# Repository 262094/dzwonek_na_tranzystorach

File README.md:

# dzwonek_na_tranzystorach
jest to aplikacja dzwonka z lat '80 typu słowik ze standardowego montażu przewlekanego THT, dzwonek został zaadaptowany na obecnie panujący trend miniaturyzacji elektroniki w połączeniu głownie montażu SMD z niektórymi elementami THT (tranzystor PNP BD140, brzęczyk bez generatora, kondensatory elektrolityczne 470uF, przycisk, złącze ARK500/2, potencjometr i kondensator ceramiczny 33nF), dzwonek udało się umieścić w wymiarach 66x37,5 (mm). W dzwonku występuje generator częstotliwości dla dzwonka złożony z przerzerzutnika Schmitta połączonego z układem Sziklaiego (wzmocnienie parametru B na wyjściu układu dla brzęczyka) oraz z przerzutnika monostabilnego jako modulatora generowanego tonu z poprzedniego przerzutnika. Układ może pracować w zasilaniu 9V DC jak i 230V AC po uprzednim zaadoptowaniu. Projekt został przygotowany do samodzielnego wytrawienia na laminacie pokrytym warstwą miedzi.

*** WIECEJ MOICH PROJEKTOW JEST DOSTEPNYCH NA MOIM KONCIE ZAPRASZAM DO ZAPOZANANIA SIE Z NIMI APLIKACJA HEALTH_CHECK ORAZ FINANCIFY***

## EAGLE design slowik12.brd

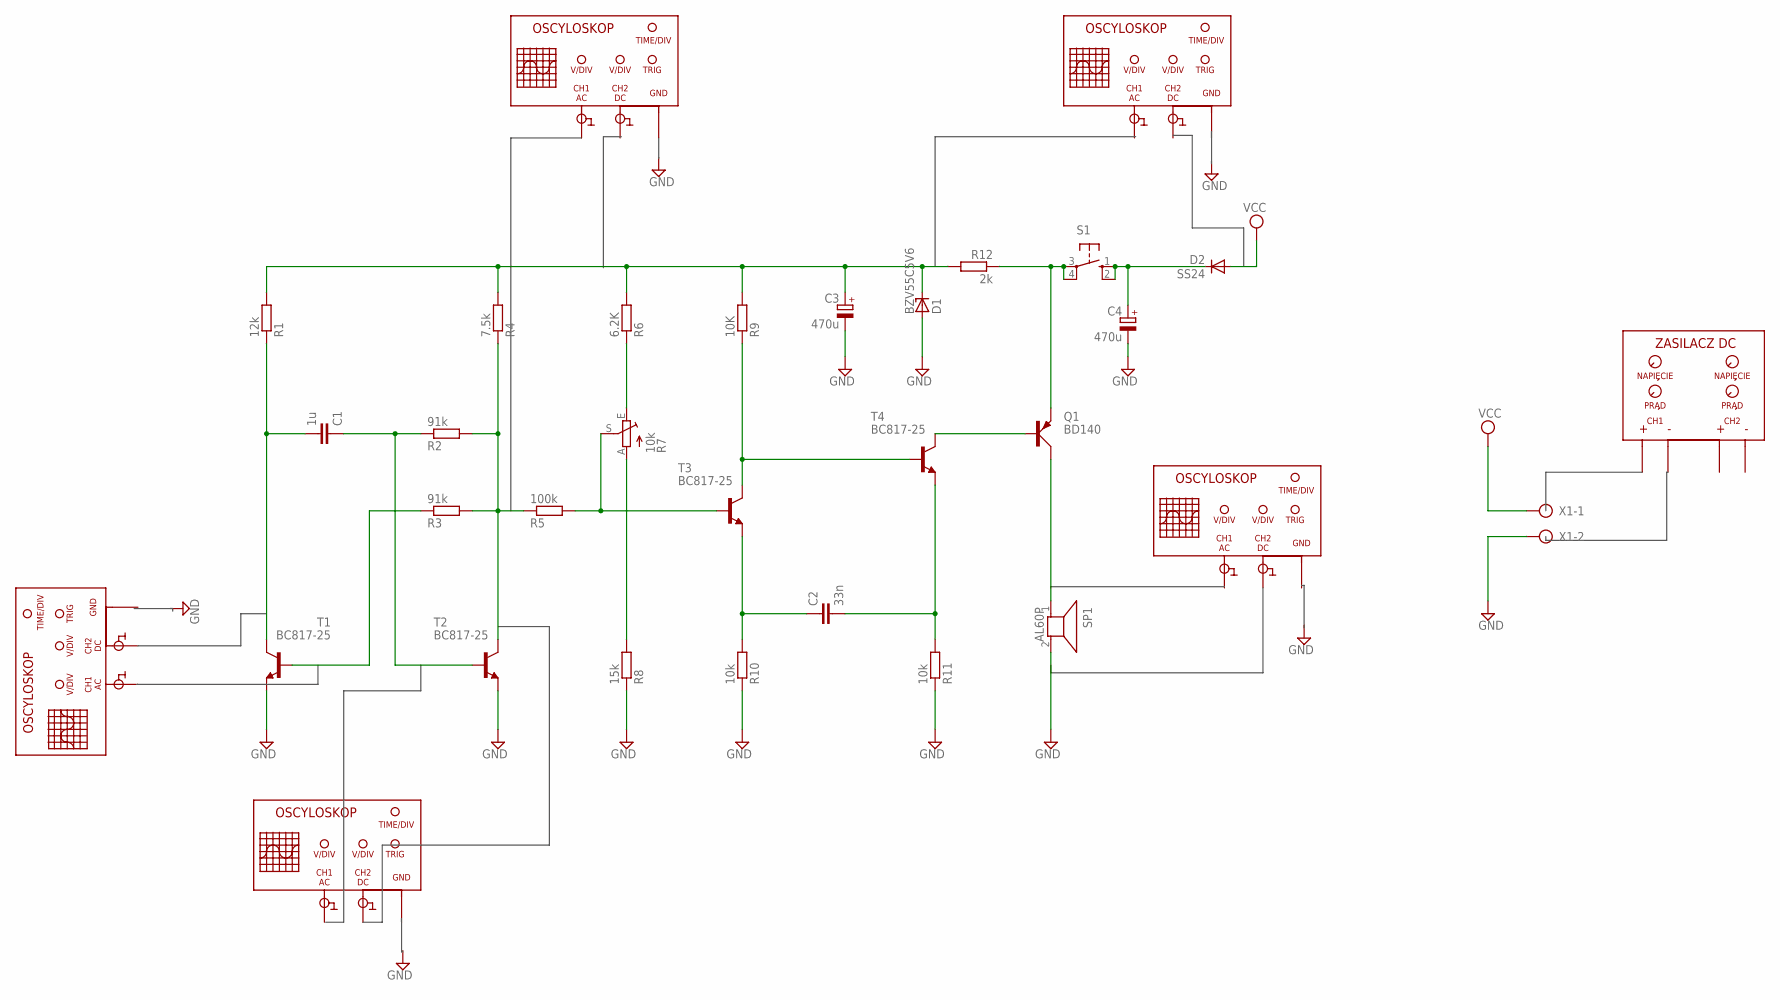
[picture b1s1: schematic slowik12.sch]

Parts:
C1: 1u; C1206
C2: 33n; C2.5-2
C3, C4: 470u; E3,5-8
D1: BZV55C5V6; SOD80C
D2: SS24; SMB
Q1: BD140; TO126AV
R1: 12k; R1206
R2, R3: 91k; R1206
R4: 7.5k; R1206
R5: 100k; R1206
R6: 6.2K; R1206
R7: 10k; PT-10
R8: 15k; R1206
R9: 10K; R1206
R10, R11: 10k; R1206
R12: 2k; R1206
S1: 10-XX; B3F-10XX
SP1: AL60P
T1, T2, T3, T4: BC817-25; SOT23-BEC
U$1, U$2, U$4, U$5, U$6: OSCYLOSKOP_DC_DC; OSCYLOSKOP
U$3: ZASILACZ
X1: AK500/2

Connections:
GND: C3.-, C4.-, D1.A, R8.1, R10.1, R11.1, SP1.2, T1.E, T2.E, X1.2
unnamed: R6.1, R7.E
unnamed: R7.A, R8.2
unnamed: Q1.E, R12.1, S1.3, S1.4 (P1)
unnamed: Q1.C, SP1.1
unnamed: Q1.B, T4.C
unnamed: C2.2, R11.2, T4.E
unnamed: C4.+, D2.C, S1.1 (S), S1.2 (S1)
unnamed: R9.1, T3.C, T4.B
unnamed: C2.1, R10.2, T3.E
unnamed: C1.2, R1.1, T1.C
unnamed: R2.2, R3.2, R4.1, R5.1, T2.C
unnamed: C1.1, R2.1, T2.B
unnamed: R3.1, T1.B
unnamed: R5.2, R7.S, T3.B
unnamed: C3.+, D1.C, R1.2, R4.2, R6.2, R9.2, R12.2
VCC: D2.A, X1.1

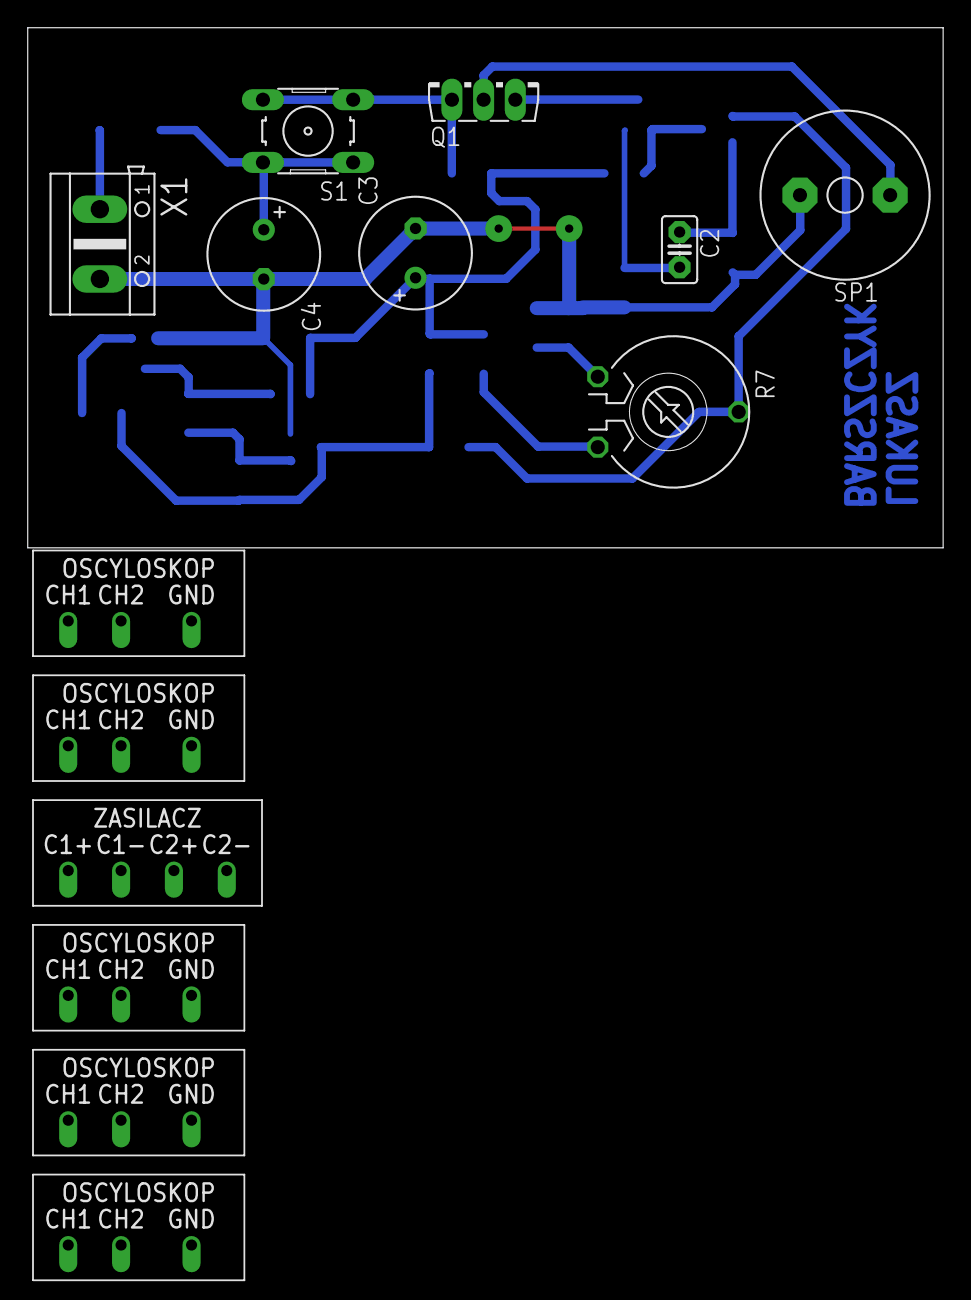
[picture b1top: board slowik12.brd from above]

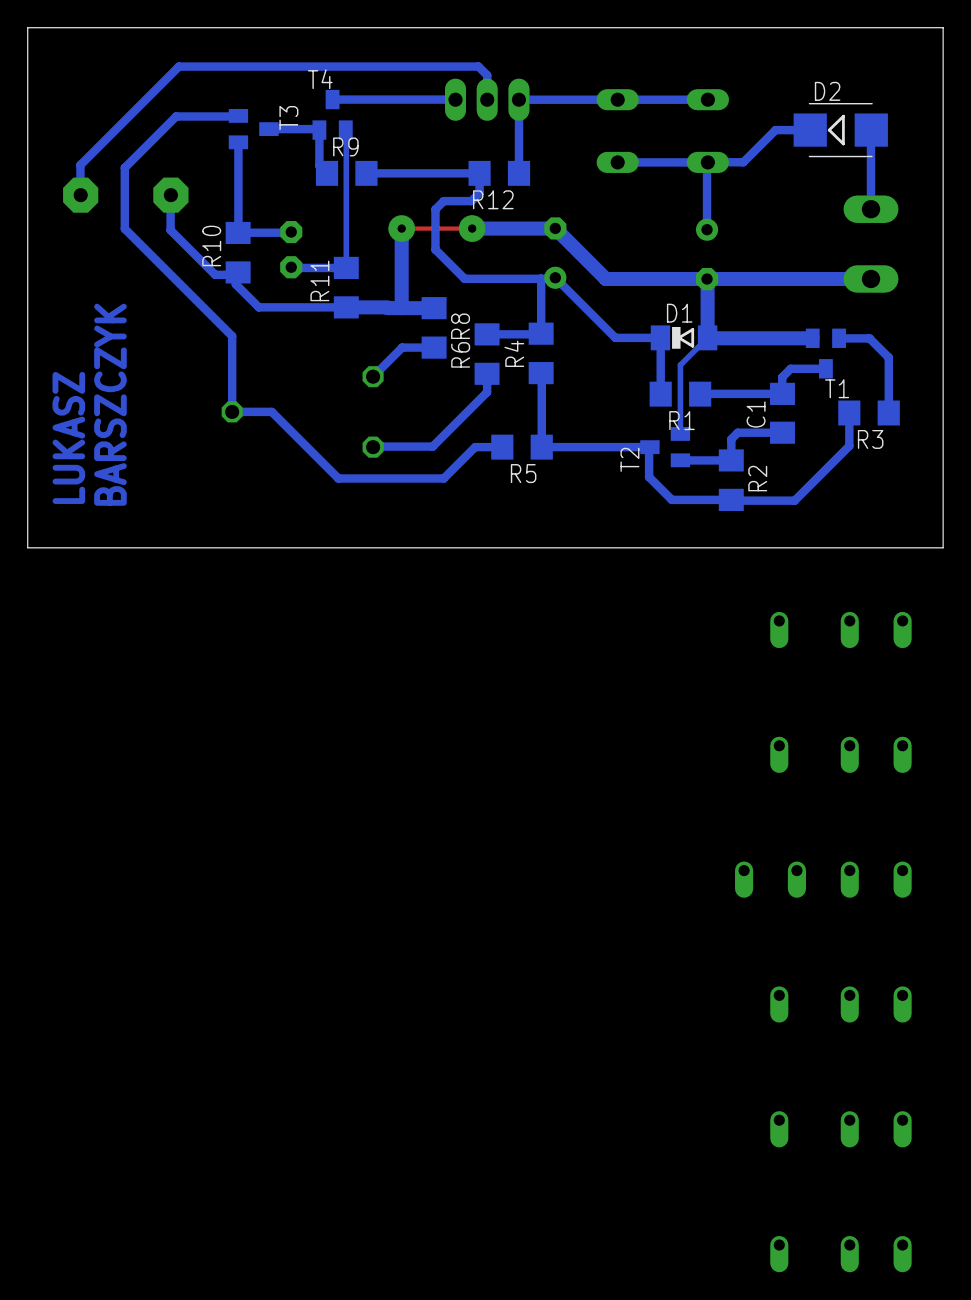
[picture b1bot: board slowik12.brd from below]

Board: 2 copper layers, 66.0 x 37.5 mm, 32 parts (18 on the bottom side), 17 nets.
